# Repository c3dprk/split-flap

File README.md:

# OMEGA Split Flap Displays
This git repository is the collection of documentation and

# img
This directory contains images we took of the actual hardware, which we used for
reverse engineering.

# pcb
This directory contains eeschma project files which document the actual circuit
board of the displays

# pdf
This directory contains pdf scans of the original documentation. There are
circuit and timing diagrams. Especially the latter ones are important when
writing software.

# uPython
This directory contains script which can be run with
[MicroPython](https://github.com/micropython/micropython) for example on an
[esp8266](http://espressif.com/en/products/hardware/esp-wroom-02/overview).

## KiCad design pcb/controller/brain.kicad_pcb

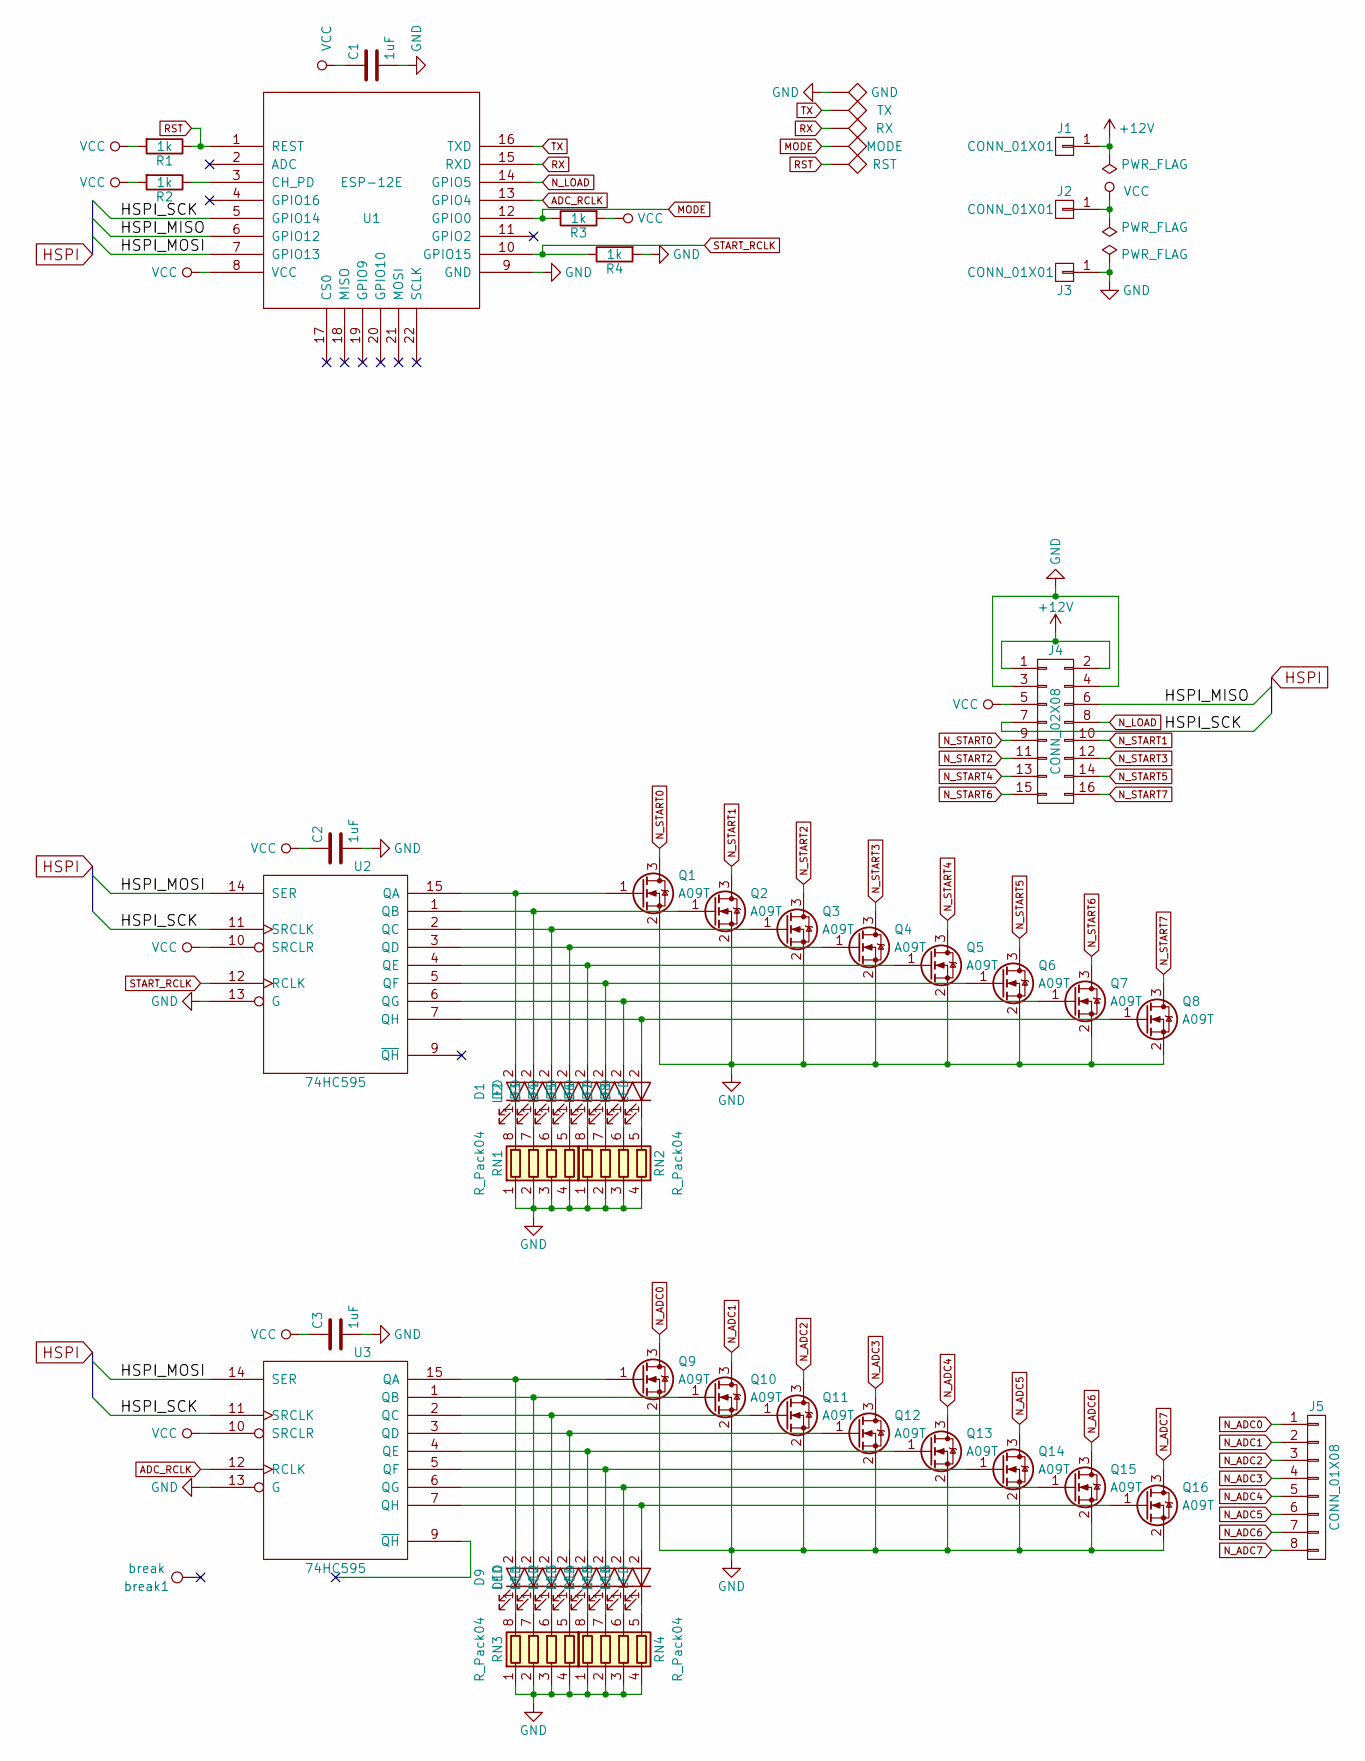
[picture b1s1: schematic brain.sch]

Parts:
C1, C2, C3: 1uF; C_0603_HandSoldering
D1, D2, D3, D4, D5, D6, D7, D8, D9, D10, D11, D12, D13, D14, D15, D16: LED; LED_0603
J1, J2, J3: CONN_01X01; 1Pin
J4: CONN_02X08; IDC_Header_SMD_16pins
J5: CONN_01X08; Pin_Header_Straight_1x08_Pitch2.54mm_SMD_Pin1Right
Q1, Q2, Q3, Q4, Q5, Q6, Q7, Q8, Q9, Q10, Q11, Q12, Q13, Q14, Q15, Q16: A09T; SOT-23
R1, R2, R3, R4: 1k; R_0603_HandSoldering
RN1, RN2, RN3, RN4: R_Pack04; R_Array_Convex_4x0603
TP1: GND; Measurement_Point_Round-SMD-Pad_Small
TP2: TX; Measurement_Point_Round-SMD-Pad_Small
TP3: RX; Measurement_Point_Round-SMD-Pad_Small
TP4: MODE; Measurement_Point_Round-SMD-Pad_Small
TP5: RST; Measurement_Point_Round-SMD-Pad_Small
U1: ESP-12E; ESP-12E_SMD
U2, U3: 74HC595; SOIC-16_3.9x9.9mm_Pitch1.27mm
break1: break

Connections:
+12V: J1.1, J4.1, J4.2
/HSPI_MISO: J4.6, U1.6 (GPIO12)
/HSPI_MOSI: U1.7 (GPIO13), U2.14 (SER), U3.14 (SER)
/HSPI_SCK: J4.7, U1.5 (GPIO14), U2.11 (SRCLK), U3.11 (SRCLK)
ADC_RCLK: U1.13 (GPIO4), U3.12 (RCLK)
GND: C1.2, C2.2, C3.2, J3.1, J4.3, J4.4, Q1.2 (S), Q2.2 (S), Q3.2 (S), Q4.2 (S), Q5.2 (S), Q6.2 (S), Q7.2 (S), Q8.2 (S), Q9.2 (S), Q10.2 (S), Q11.2 (S), Q12.2 (S), Q13.2 (S), Q14.2 (S), Q15.2 (S), Q16.2 (S), R4.2, RN1.1 (R1.1), RN1.2 (R2.1), RN1.3 (R3.1), RN1.4 (R4.1), RN2.1 (R1.1), RN2.2 (R2.1), RN2.3 (R3.1), RN2.4 (R4.1), RN3.1 (R1.1), RN3.2 (R2.1), RN3.3 (R3.1), RN3.4 (R4.1), RN4.1 (R1.1), RN4.2 (R2.1), RN4.3 (R3.1), RN4.4 (R4.1), TP1.1, U1.9 (GND), U2.8 (GND), U2.13 (G), U3.8 (GND), U3.13 (G)
MODE: R3.1, TP4.1, U1.12 (GPIO0)
N_ADC0: J5.1, Q9.3 (D)
N_ADC1: J5.2, Q10.3 (D)
N_ADC2: J5.3, Q11.3 (D)
N_ADC3: J5.4, Q12.3 (D)
N_ADC4: J5.5, Q13.3 (D)
N_ADC5: J5.6, Q14.3 (D)
N_ADC6: J5.7, Q15.3 (D)
N_ADC7: J5.8, Q16.3 (D)
N_LOAD: J4.8, U1.14 (GPIO5)
N_START0: J4.9, Q1.3 (D)
N_START1: J4.10, Q2.3 (D)
N_START2: J4.11, Q3.3 (D)
N_START3: J4.12, Q4.3 (D)
N_START4: J4.13, Q5.3 (D)
N_START5: J4.14, Q6.3 (D)
N_START6: J4.15, Q7.3 (D)
N_START7: J4.16, Q8.3 (D)
unnamed: D1.1 (K), RN1.8 (R1.2)
unnamed: D1.2 (A), Q1.1 (G), U2.15 (QA)
unnamed: D2.1 (K), RN1.7 (R2.2)
unnamed: D2.2 (A), Q2.1 (G), U2.1 (QB)
unnamed: D3.1 (K), RN1.6 (R3.2)
unnamed: D3.2 (A), Q3.1 (G), U2.2 (QC)
unnamed: D4.1 (K), RN1.5 (R4.2)
unnamed: D4.2 (A), Q4.1 (G), U2.3 (QD)
unnamed: D5.1 (K), RN2.8 (R1.2)
unnamed: D5.2 (A), Q5.1 (G), U2.4 (QE)
unnamed: D6.1 (K), RN2.7 (R2.2)
unnamed: D6.2 (A), Q6.1 (G), U2.5 (QF)
unnamed: D7.1 (K), RN2.6 (R3.2)
unnamed: D7.2 (A), Q7.1 (G), U2.6 (QG)
unnamed: D8.1 (K), RN2.5 (R4.2)
unnamed: D8.2 (A), Q8.1 (G), U2.7 (QH)
unnamed: D9.1 (K), RN3.8 (R1.2)
unnamed: D9.2 (A), Q9.1 (G), U3.15 (QA)
unnamed: D10.1 (K), RN3.7 (R2.2)
unnamed: D10.2 (A), Q10.1 (G), U3.1 (QB)
unnamed: D11.1 (K), RN3.6 (R3.2)
unnamed: D11.2 (A), Q11.1 (G), U3.2 (QC)
unnamed: D12.1 (K), RN3.5 (R4.2)
unnamed: D12.2 (A), Q12.1 (G), U3.3 (QD)
unnamed: D13.1 (K), RN4.8 (R1.2)
unnamed: D13.2 (A), Q13.1 (G), U3.4 (QE)
unnamed: D14.1 (K), RN4.7 (R2.2)
unnamed: D14.2 (A), Q14.1 (G), U3.5 (QF)
unnamed: D15.1 (K), RN4.6 (R3.2)
unnamed: D15.2 (A), Q15.1 (G), U3.6 (QG)
unnamed: D16.1 (K), RN4.5 (R4.2)
unnamed: D16.2 (A), Q16.1 (G), U3.7 (QH)
unnamed: R2.1, U1.3 (CH_PD)
RST: R1.1, TP5.1, U1.1 (REST)
RX: TP3.1, U1.15 (RXD)
START_RCLK: R4.1, U1.10 (GPIO15), U2.12 (RCLK)
TX: TP2.1, U1.16 (TXD)
VCC: C1.1, C2.1, C3.1, J2.1, J4.5, R1.2, R2.2, R3.2, U1.8 (VCC), U2.10 (SRCLR), U2.16 (VCC), U3.10 (SRCLR), U3.16 (VCC)

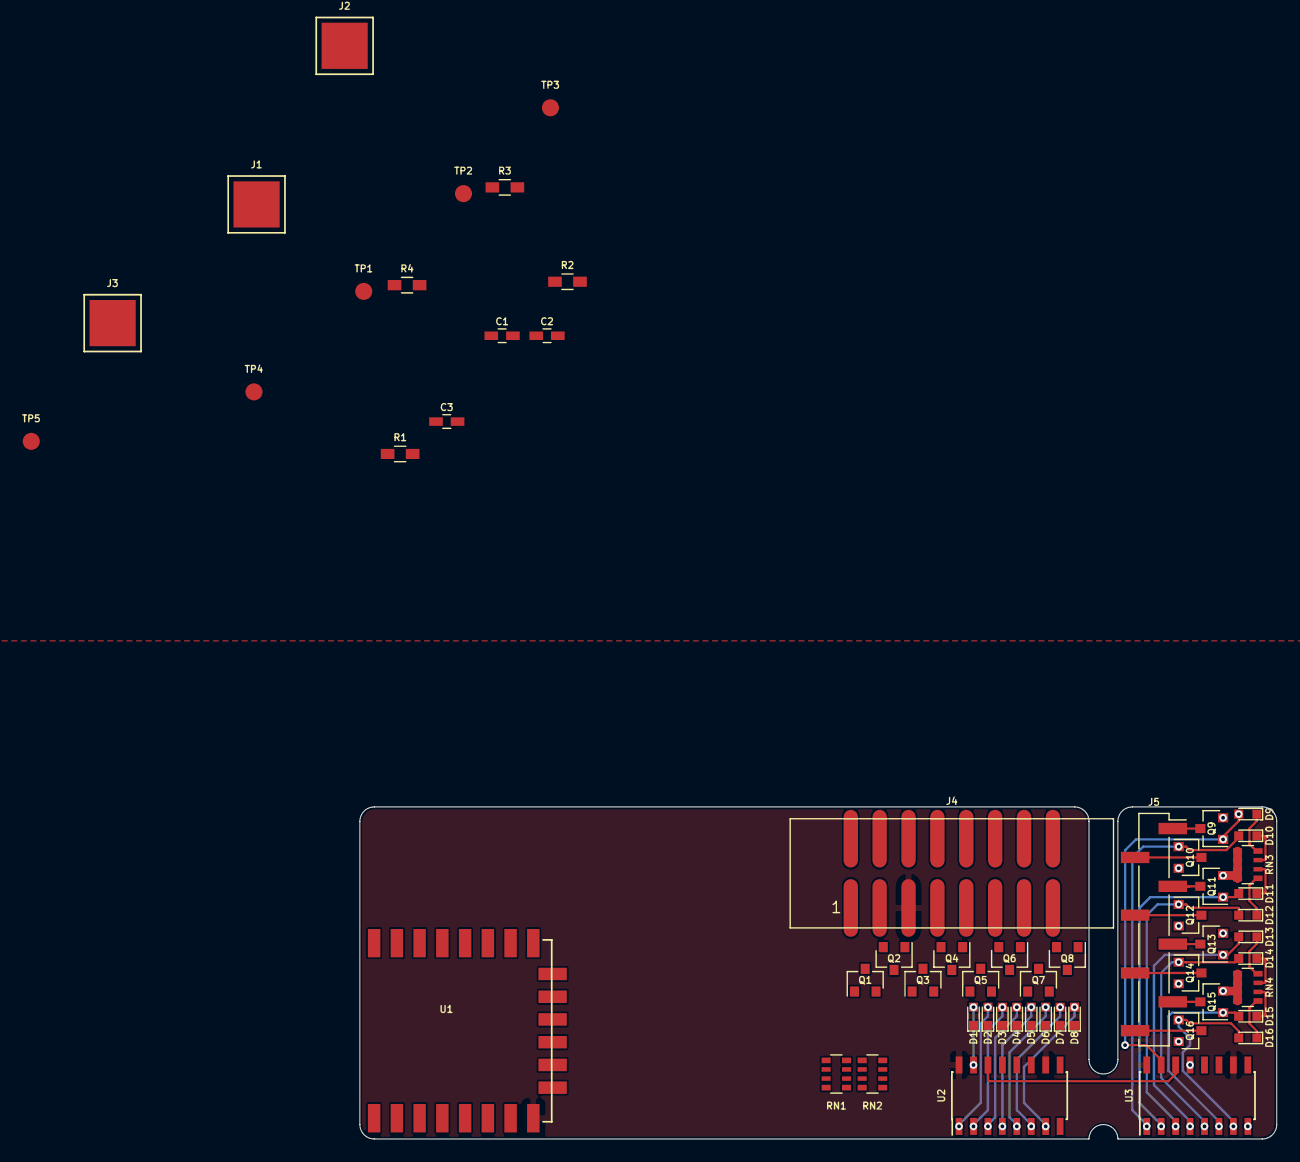
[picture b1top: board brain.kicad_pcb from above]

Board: 2 copper layers, 80.6 x 29.2 mm, 56 parts (0 on the bottom side), 62 nets.

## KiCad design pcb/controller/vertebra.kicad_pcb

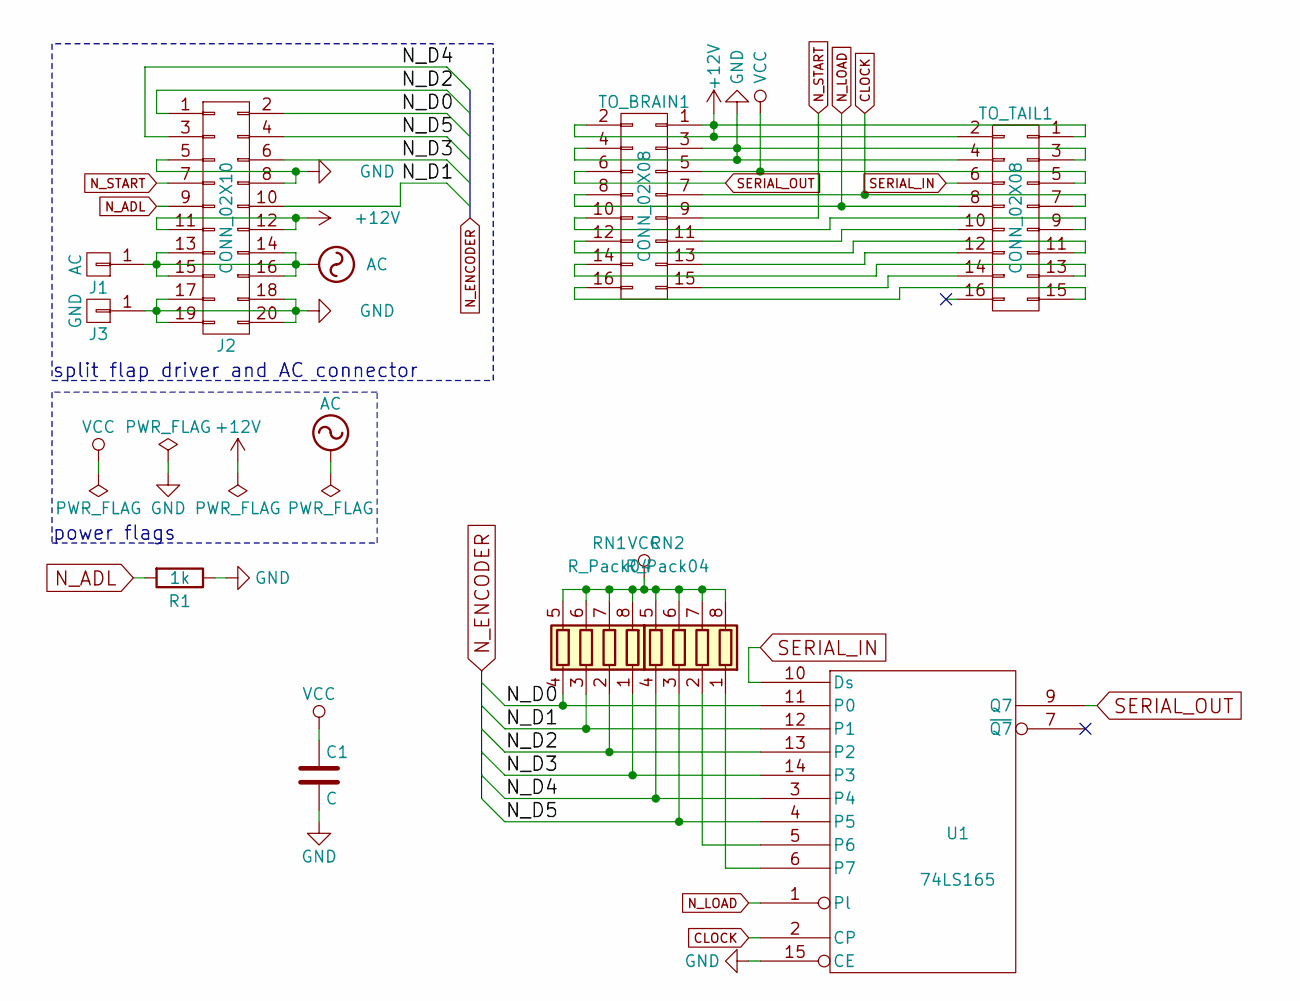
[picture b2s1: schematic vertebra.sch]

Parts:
C1: C; C_0603_HandSoldering
J1: AC; 1Pin
J2: CONN_02X10; Pin_Header_Straight_2x10_Pitch2.54mm_SMD
J3: GND; 1Pin
R1: 1k; R_0603_HandSoldering
RN1, RN2: R_Pack04; R_Array_Convex_4x0603
TO_BRAIN1: CONN_02X08; Pin_Header_Straight_2x08_Pitch2.54mm_SMD
TO_TAIL1: CONN_02X08; Pin_Header_Straight_2x08_Pitch2.54mm_SMD
U1: 74LS165; SOIC-16_3.9x9.9mm_Pitch1.27mm

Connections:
+12V: J2.11, J2.12, TO_BRAIN1.1, TO_BRAIN1.2, TO_TAIL1.1, TO_TAIL1.2
/N_D0: J2.2, RN1.4 (R4.1), U1.11 (P0)
/N_D1: J2.10, RN1.3 (R3.1), U1.12 (P1)
/N_D2: J2.1, RN1.2 (R2.1), U1.13 (P2)
/N_D3: J2.6, RN1.1 (R1.1), U1.14 (P3)
/N_D4: J2.3, RN2.4 (R4.1), U1.3 (P4)
/N_D5: J2.4, RN2.3 (R3.1), U1.4 (P5)
AC: J1.1, J2.13, J2.14, J2.15, J2.16
CLOCK: TO_BRAIN1.7, TO_TAIL1.7, U1.2 (CP)
GND: C1.2, J2.5, J2.8, J2.17, J2.18, J2.19, J2.20, J3.1, R1.1, TO_BRAIN1.3, TO_BRAIN1.4, TO_TAIL1.3, TO_TAIL1.4, U1.8 (GND), U1.15 (CE)
N_ADL: J2.9, R1.2
N_LOAD: TO_BRAIN1.8, TO_TAIL1.8, U1.1 (Pl)
N_START: J2.7, TO_BRAIN1.9
unnamed: RN2.1 (R1.1), U1.6 (P7)
unnamed: RN2.2 (R2.1), U1.5 (P6)
unnamed: TO_BRAIN1.10, TO_TAIL1.9
unnamed: TO_BRAIN1.11, TO_TAIL1.10
unnamed: TO_BRAIN1.12, TO_TAIL1.11
unnamed: TO_BRAIN1.13, TO_TAIL1.12
unnamed: TO_BRAIN1.14, TO_TAIL1.13
unnamed: TO_BRAIN1.15, TO_TAIL1.14
unnamed: TO_BRAIN1.16, TO_TAIL1.15
SERIAL_IN: TO_TAIL1.6, U1.10 (Ds)
SERIAL_OUT: TO_BRAIN1.6, U1.9 (Q7)
VCC: C1.1, RN1.5 (R4.2), RN1.6 (R3.2), RN1.7 (R2.2), RN1.8 (R1.2), RN2.5 (R4.2), RN2.6 (R3.2), RN2.7 (R2.2), RN2.8 (R1.2), TO_BRAIN1.5, TO_TAIL1.5, U1.16 (VCC)

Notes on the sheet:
split flap driver and AC connector
power flags

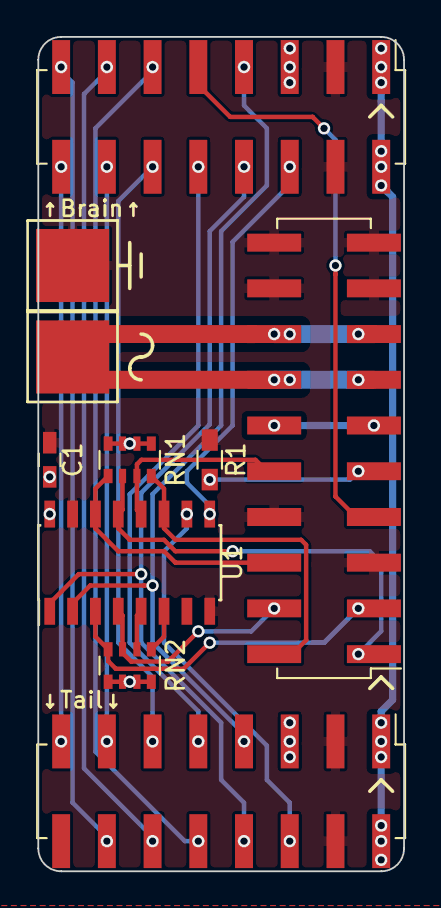
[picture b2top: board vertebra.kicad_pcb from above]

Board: 2 copper layers, 20.3 x 46.4 mm, 10 parts (0 on the bottom side), 25 nets.

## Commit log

2017-07-30 added images
2017-07-30 added eeschame schematic
2017-07-31 added some pdfs from https://fallblatt.blogspot.de/
2017-07-31 preliminary schematic
2017-07-31 added some more pdfs from https://fallblatt.blogspot.de/
2017-07-31 very updated schematic
2017-07-31 freshly exported
2017-07-31 rotated 90 degree
2017-08-30 somethingsomething i dunno
2017-08-30 moved svg
2017-08-30 removed unused controller schematics
2017-08-30 moved pcb files
2017-09-02 rearranged parts and refernce labels '
2017-09-02 added example script for micropython
2017-09-02 plotted schematic
2017-09-02 adde readme
2017-09-02 added license and stuff
2017-09-02 includes schematic images
2017-09-03 made schematic plot an png
2017-09-03 added NTP update every whole hour
2017-09-03 moved files for driver board into sepearate direcotry
2017-09-06 added "exception handling"
2017-09-06 added stuff for controller pcb
2017-09-12 ignore backup files
2017-09-12 designed v0.1 of brain board
2017-09-12 modified vertebra to match brain
2017-09-12 added cached libs to compensate in case of missing libs
2017-09-12 added custom break away pad
2017-10-21 controller code
2017-11-01 quickpush
2017-12-16 begins to further develop controller
2018-01-04 working prototype
2018-01-04 2 obvious fuckups, untested - still a shitty late night hack
2018-01-05 general improvements
2018-01-05 webserver stuff
2018-01-06 personal flap names
2018-01-06 added electronics documentation
2018-01-06 some notes
